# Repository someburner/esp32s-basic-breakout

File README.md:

# ESP32S Breakout

Bare-minimum breakout board for ESP32S. Info taken from Sparkfun's [ESP32S hookup guide](https://www.sparkfun.com/news/2017). Board not yet tested, but I have tested everything in the schematic using an ESP32S with soldered connections.

# Componenents

* AI-Thinker ESP32S
* [AMS1117](https://www.amazon.com/SUNKEE-AMS1117-Voltage-Regulator-AMS1117-3-3V/dp/B00898NGL0) or similar
* 0805 Caps - 10u (x1), 22u (x1), 0.1u (x1)
* 0805 Resistors - 10K (x2)

# Connectors

* 0.1" male headers - 14x2, 10x1, 2x1 (for VIN if not using DC Jack)
* SPDT slide switch for selecting Flash/Run modes
* JST-XH 3-in connector for UART (TX0/RX0/GND)
* [Side-mount push button](http://www.digikey.com/product-search/en?keywords=1825027-5)
* [3.5mmx1.3mm DC Jack](https://www.aliexpress.com/item/DC-Power-adapter-dc-jack-connector-DC002-3-5-X-1-3-mm-50-pcs-lot/32601221205.html?spm=2114.13010608.0.0.YeQ6Bo)
* [2A AC Adapter](https://www.aliexpress.com/item/5-pcs-Free-Shipping-5V-DC-2A-Wall-Adapter-AC-Power-Supply-5VDC-2A-3-5mm/1048925486.html?spm=2114.13010608.0.0.KU5QDf)

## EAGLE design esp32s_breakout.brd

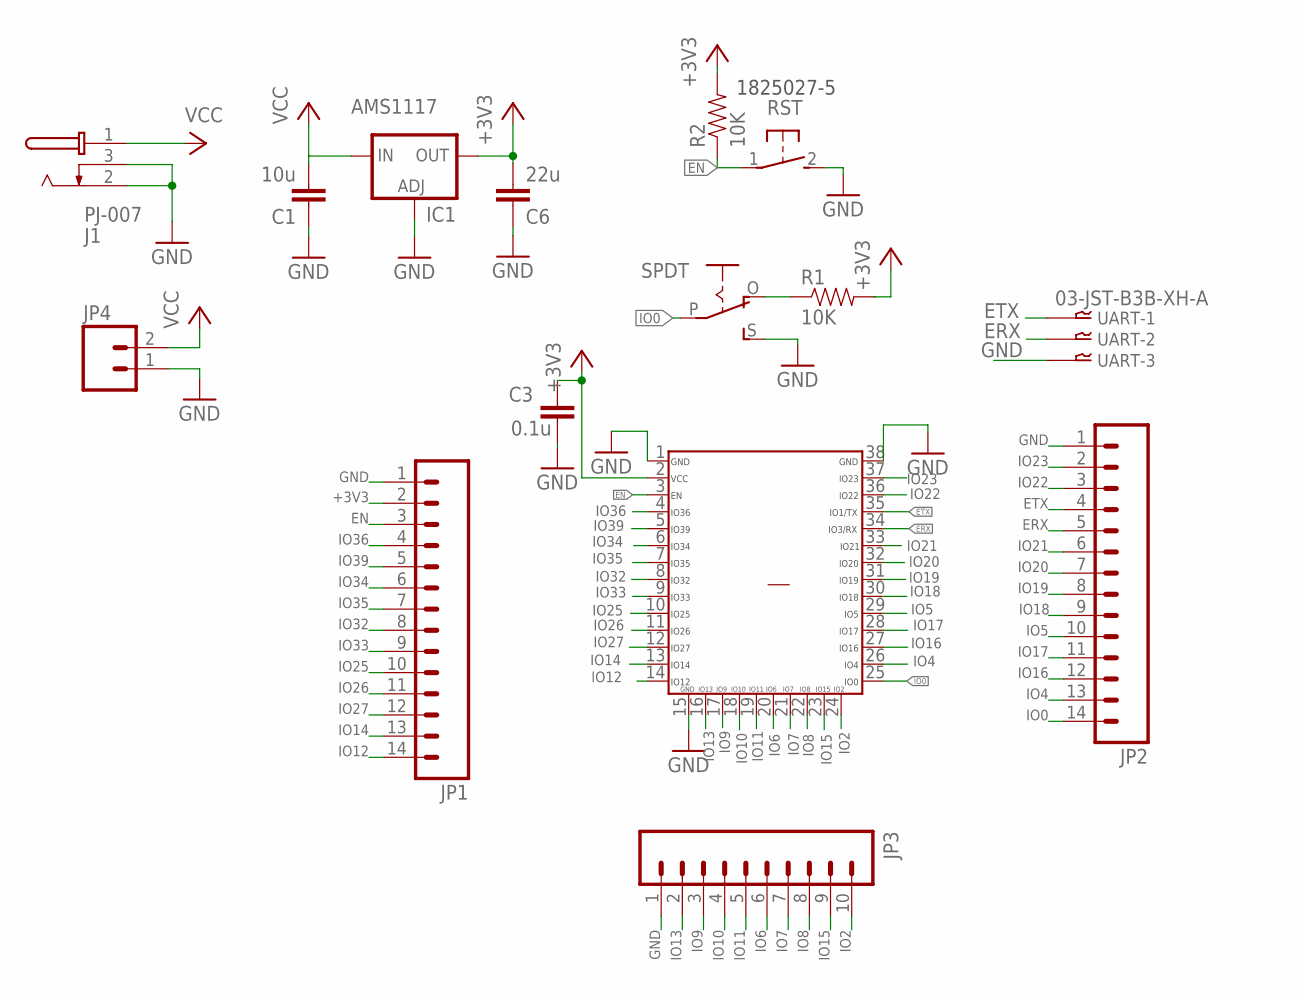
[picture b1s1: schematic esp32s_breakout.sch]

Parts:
C1: 10u; 0805-CAP-LARGEPADS
C3: 0.1u; 0805
C6: 22u; 0805
IC1: AMS1117; SOT223
J1: PJ-007
JP1, JP2: M14; 1X14
JP3: M10SILK_FEMALE_PTH; 1X10
JP4: M02PTH; 1X02
R1, R2: 10K; 0805
RST: 1825027-XBLK-152; 1825027-152
SPDT: EG1218S; EG1218
U$1: ESP32S32S; ESP32
UART: 03-JST-B3B-XH-A; B3B-XH

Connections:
+3V3: C3.1, C6.2, IC1.4 (OUT), JP1.2, R1.2, R2.2, U$1.2
EN: JP1.3, R2.1, RST.1, U$1.3
ERX: JP2.5, U$1.34, UART.P$2
ETX: JP2.4, U$1.35, UART.P$1
GND: C1.1, C3.2, C6.1, IC1.1 (ADJ), J1.2 (S), J1.3 (SS), JP1.1, JP2.1, JP3.1, JP4.1, RST.2 (S), SPDT.S, U$1.1, U$1.15, U$1.38, UART.P$3
IO0: JP2.14, SPDT.P, U$1.25
IO2: JP3.10, U$1.24
IO4: JP2.13, U$1.26
IO5: JP2.10, U$1.29
IO6: JP3.6, U$1.20
IO7: JP3.7, U$1.21
IO8: JP3.8, U$1.22
IO9: JP3.3, U$1.17
IO10: JP3.4, U$1.18
IO11: JP3.5, U$1.19
IO12: JP1.14, U$1.14
IO13: JP3.2, U$1.16
IO14: JP1.13, U$1.13
IO15: JP3.9, U$1.23
IO16: JP2.12, U$1.27
IO17: JP2.11, U$1.28
IO18: JP2.9, U$1.30
IO19: JP2.8, U$1.31
IO20: JP2.7, U$1.32
IO21: JP2.6, U$1.33
IO22: JP2.3, U$1.36
IO23: JP2.2, U$1.37
IO25: JP1.10, U$1.10
IO26: JP1.11, U$1.11
IO27: JP1.12, U$1.12
IO32: JP1.8, U$1.8
IO33: JP1.9, U$1.9
IO34: JP1.6, U$1.6
IO35: JP1.7, U$1.7
IO36: JP1.4, U$1.4
IO39: JP1.5, U$1.5
unnamed: R1.1, SPDT.O
P$39: U$1.GNDTHRM
VCC: C1.2, IC1.3 (IN), J1.1 (T), JP4.2

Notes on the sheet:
1825027-5

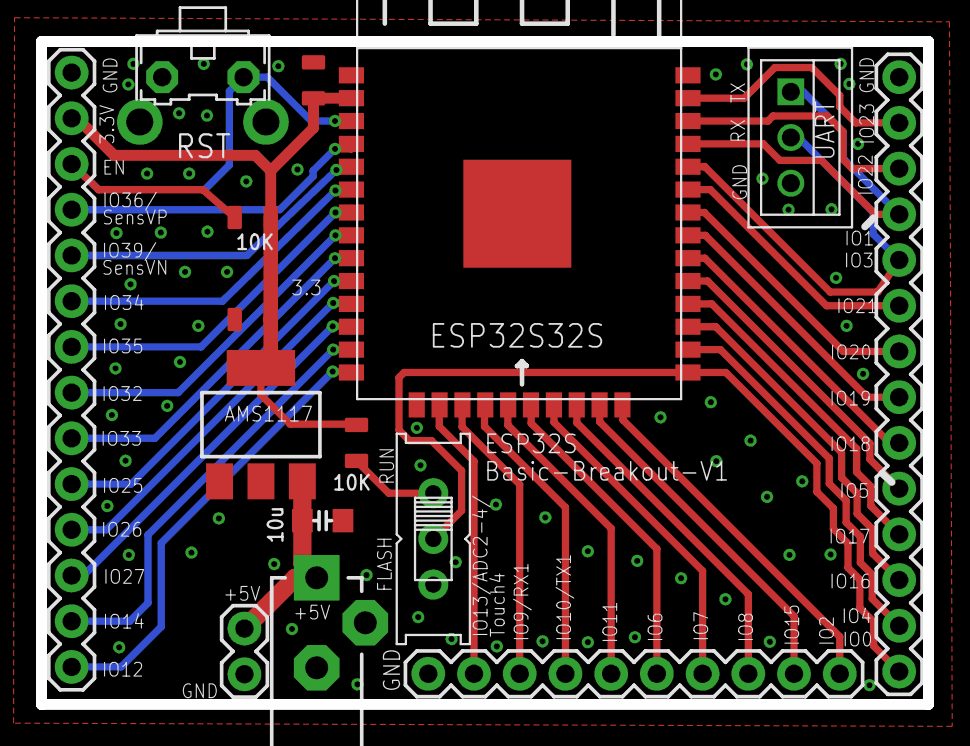
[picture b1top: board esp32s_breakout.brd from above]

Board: 2 copper layers, 49.3 x 36.8 mm, 15 parts (0 on the bottom side), 38 nets.

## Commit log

2016-10-30 initial v
2016-10-30 add rendered png
2016-10-30 squeeze to get under 5cm

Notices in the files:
parts and their libraries:
con-cruistack: Copyright (C) 2008, Bob Starr
SparkFun-Connectors: Licensing: Creative Commons ShareAlike 4.0 International - https://creativecommons.org/licenses/by-sa/4.0
